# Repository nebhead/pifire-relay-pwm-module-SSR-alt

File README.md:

# PiFire Solid State Relay (SSR) Module PCB ALT (v1.0.0-alt) KiCad Files

## What is this? 

This PCB is designed to support SSR relays for controlling incoming Power(L) to the Igniter and Auger.  This board also has circuitry to support a 12V PWM fan.  This board uses compact solid state relays that are able to handle high power. This is an alternative to using an off the shelf relay module which simplifies the wiring and even allows you to use the OEM harness.

This version of the board was designed with help from user @labmonkeyrat on Discord. PCB mounted fuses have been removed, preferring inline fuses external to the board. The fan power is controlled from the high side (12V) instead of ground (original design).  

The design intent for this board was to make a DIY accessible PCB that can be more easily put together by the maker/enthusiast of almost any skill level.  Full size components are used in most cases and most (if not all) parts should be readily available to order online.  See the [Interactive BOM](#interactive-bom) for more details about the parts used and links to order.

### Important Notes

This PCB is intended to be used with the 4.0.x PCB design ([linked below](#links-to-the-pcbs-in-this-family-of-pifire-boards)) in conjunction with v1.8.x or later of the PiFire software.

The G3MB Relay footprints have been left out of this release because they were sourced from SnapMagic (for free), but are not licensed for re-distribution.  If you plan to edit this board, you may need to source those files from SnapMagic directly and add them to this project in the G3MB folder.

### What is PiFire? 

PiFire is a SBC based Pellet Smoker Controller.  More details can be found [here](https://nebhead.github.io/PiFire) or [at the GitHub repo](https://github.com/nebhead/pifire). 

## What's in this Repository?

### KiCad Project Files 
In this repository you will find the latest KiCad design files for the  PCB.  Simply load the project file (.kicad_pro) into the KiCad software and you should be able to edit as needed.  Or if you just want to get this board made, jump to the production section below.

### Interactive BOM

There is an interactive BOM located in the [/bom](bom/) folder which details the parts and provides some pin information as well.  Use this to gather the components you may need to build this board out and refer back to it for placement help.    

[BOM + Pin Info](https://nebhead.github.io/pifire-relay-pwm-module-SSR-alt)

_This is a standalone HTML file that was autogenerated by the excellent plugin for KiCad. See the plugin here: [https://github.com/openscopeproject/InteractiveHtmlBom](https://github.com/openscopeproject/InteractiveHtmlBom)_

### PDF of the Schematic

Preview the schematic in PDF format here: [Schematic](schematic.pdf)

### PWM Fan Pinout

The PWM fan pinout is using a standard 4-pin fan connector.  It's recommended to source the headers with retaining clip to ensure that the fan doesn't easily come unplugged.  JST headers can be used as well. 

### JLCPCB Production Files

If you wish to get these PCBs made by JLCPCB, the production files are provided in the `/production` folder.  For convenience, the file `production.zip` can simply be uploaded to JLCPCB to make it super easy to order boards.

Drop the zip file onto the order page, wait for it to upload then simply continue to order the board.  Optionally, select different board color, PCB quantity, surface finish, etc.  Most of the default settings should be sufficient. 

### Links to the PCBs in this family of PiFire Boards

This PCB is part of a family of PCBs that can be used together to create  a full PiFire system.  Generally speaking you need the Main Module/Board, a Relay Control Board and a Probe Device board to have a basic PiFire system.  

**Main Module/Board** (required)
* [Main Board v4.0.x](https://github.com/nebhead/pifire-main-module-nopwr)

**Relay/Fan Control Boards** (choose one)
* [Mechanical Relay Module](https://github.com/nebhead/pifire-relay-module)
* [Solid State Relay Module](https://github.com/nebhead/pifire-relay-module-ssr)
* [Solid State Relay + PWM Fan Module](https://github.com/nebhead/pifire-relay-pwm-module-ssr) - Original Design
* [Solid State Relay + PWM Fan Module Alternate](https://github.com/nebhead/pifire-relay-pwm-module-ssr-alt) - Updated Design (Designed with help from @labmonkeyrat on Discord)

**Probe Device Board** (optional)
* [ADS Board](https://github.com/nebhead/pifire-ads-board) 

### 3D Printable Enclosures/Boxes 

With all of the 3D Prints for PiFire, a higher temperature filament such as PETG should be used.  PLA generally won't stand up to the temperatures that the components may be exposed to outdoors and near a hot smoker.  

#### Enclosure

Included here is an initial revision of the enclosure for this PCB.  The current models should be considered still in development and may have alignment challenges, etc. 

Except for the mounting wings, the majority of bolts to be used with this enclosure are M3. 

* STL: [Base](/printables/PiFire-v4-Relay-Base.stl)
* STL: [Lid](/printables/PiFire-v4-Relay-Lid.stl)
* OnShape: [Enclosure Original Models](https://cad.onshape.com/documents/03559f76f7adf190bf6f1259/w/7529cb0e4cd69db1a6a15202/e/07d5f9d46dc8f2b9e7dd655f?renderMode=0&uiState=66e11de950d7684b88999a0f)

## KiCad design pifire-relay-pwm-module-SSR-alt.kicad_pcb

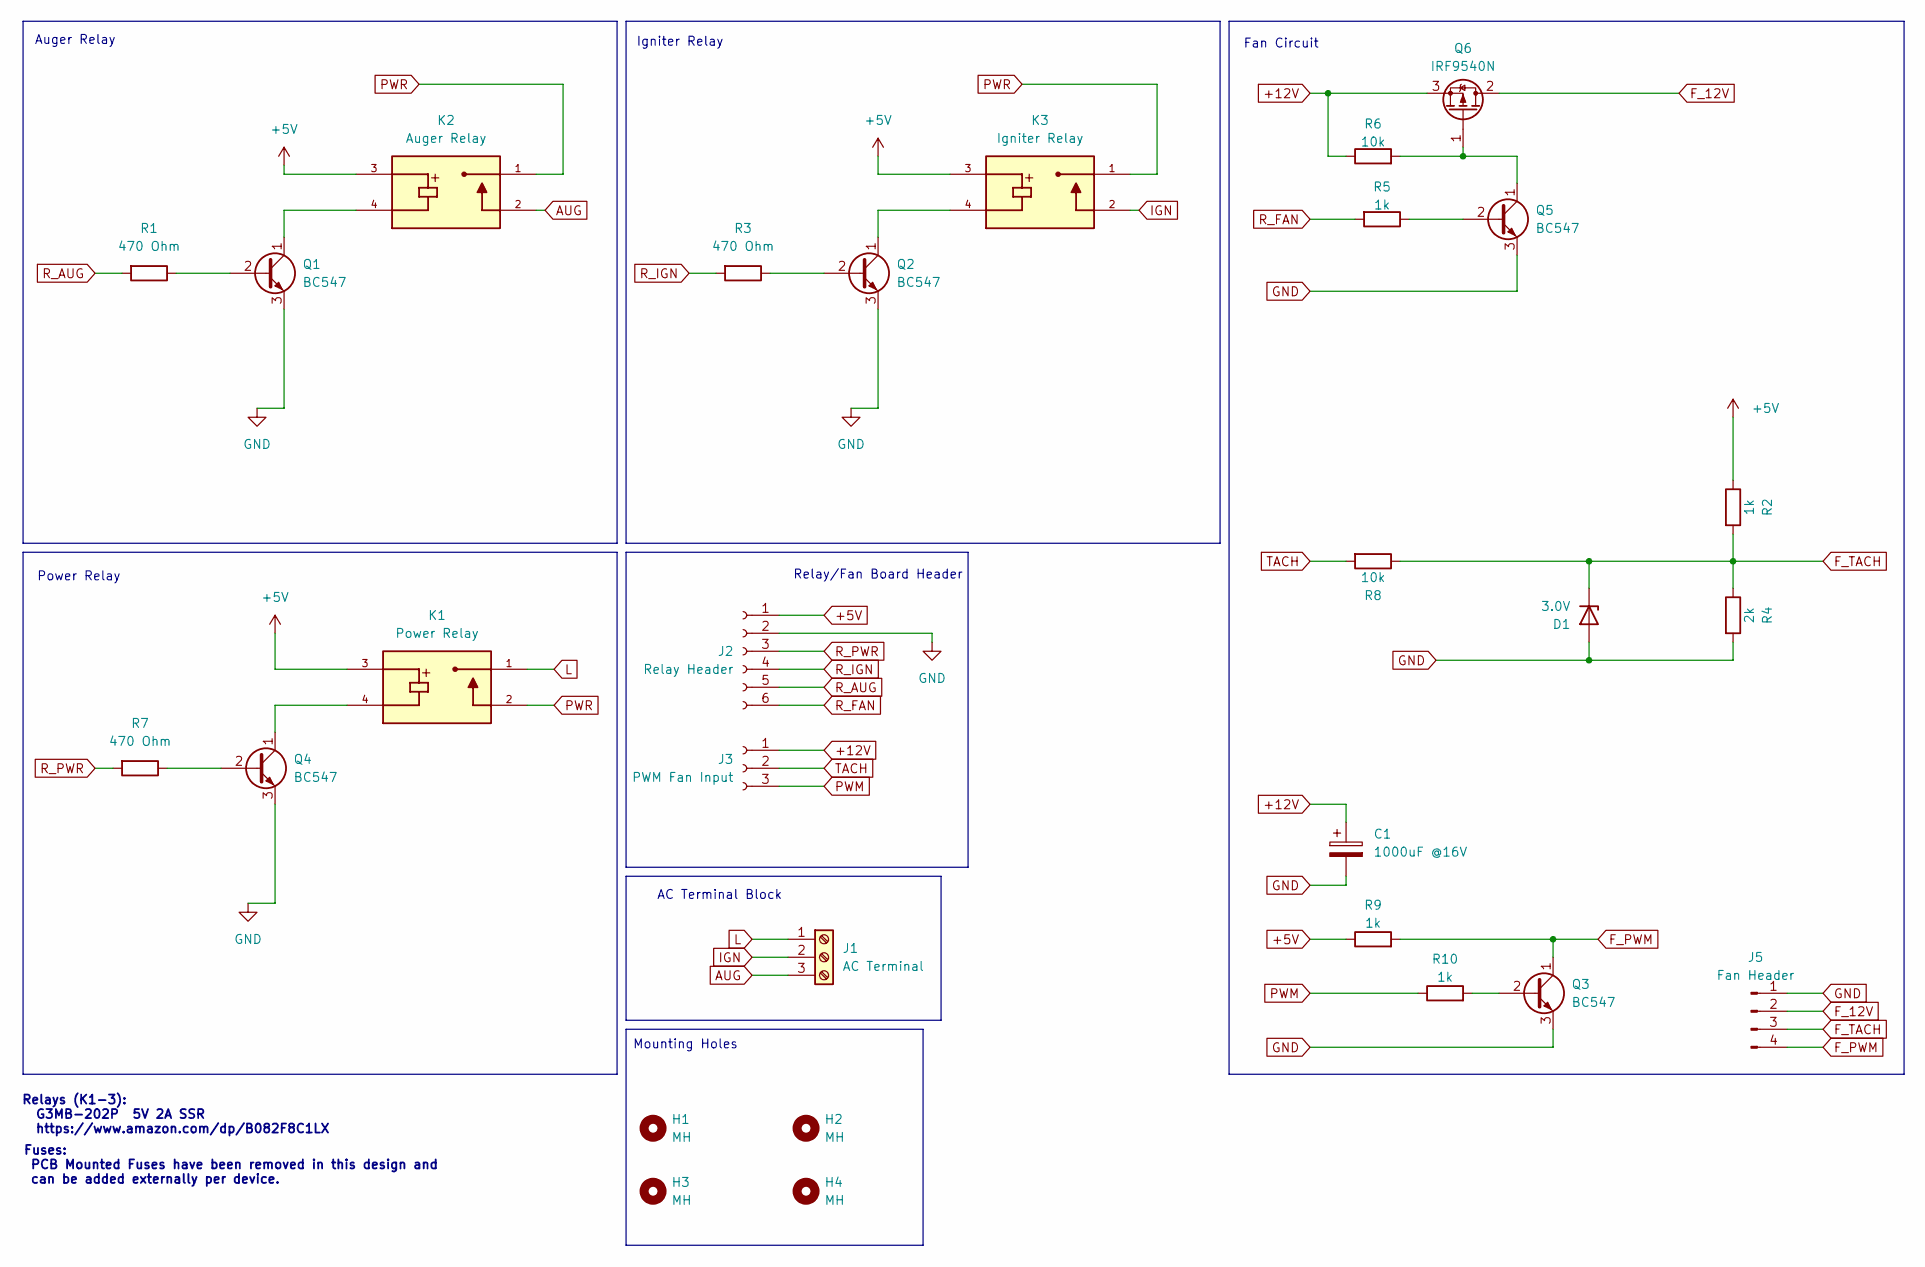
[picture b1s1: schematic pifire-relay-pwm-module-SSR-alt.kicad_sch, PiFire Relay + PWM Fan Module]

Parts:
C1: 1000uF @16V; CP_Radial_D6.3mm_P2.50mm
D1: 3.0V; D_DO-41_SOD81_P7.62mm_Horizontal
H1, H2, H3, H4: MH; MountingHole_3.2mm_M3
J1: AC Terminal; TerminalBlock_bornier-3_P5.08mm
J2: Relay Header; JST_XH_B6B-XH-A_1x06_P2.50mm_Vertical
J3: PWM Fan Input; JST_XH_B3B-XH-A_1x03_P2.50mm_Vertical
J5: Fan Header; FanPinHeader_1x04_P2.54mm_Vertical
K1: Power Relay; RELAY_G3MB-202PDC5; PARTREV J091-E1-1A
K2: Auger Relay; RELAY_G3MB-202PDC5; PARTREV J091-E1-1A
K3: Igniter Relay; RELAY_G3MB-202PDC5; PARTREV J091-E1-1A
Q1, Q2, Q3, Q4, Q5: BC547; TO-92L_Inline
Q6: IRF9540N; TO-220-3_Vertical
R1, R3, R7: 470 Ohm; R_Axial_DIN0207_L6.3mm_D2.5mm_P7.62mm_Horizontal
R2, R5, R9, R10: 1k; R_Axial_DIN0207_L6.3mm_D2.5mm_P7.62mm_Horizontal
R4: 2k; R_Axial_DIN0207_L6.3mm_D2.5mm_P7.62mm_Horizontal
R6, R8: 10k; R_Axial_DIN0207_L6.3mm_D2.5mm_P7.62mm_Horizontal

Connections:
+5V: J2.1, K1.3, K2.3, K3.3, R2.1, R9.1
+12V: C1.1, J3.1, Q6.3 (S), R6.1
AUG: J1.3, K2.2
F_12V: J5.2, Q6.2 (D)
F_PWM: J5.4, Q3.1 (C), R9.2
F_TACH: D1.1 (K), J5.3, R2.2, R4.1, R8.1
GND: C1.2, D1.2 (A), J2.2, J5.1, Q1.3 (E), Q2.3 (E), Q3.3 (E), Q4.3 (E), Q5.3 (E), R4.2
IGN: J1.2, K3.2
L: J1.1, K1.1
unnamed: Q1.2 (B), R1.1
unnamed: K2.4, Q1.1 (C)
unnamed: Q2.2 (B), R3.1
unnamed: K3.4, Q2.1 (C)
unnamed: Q3.2 (B), R10.2
unnamed: Q4.2 (B), R7.1
unnamed: K1.4, Q4.1 (C)
unnamed: Q5.2 (B), R5.1
unnamed: Q5.1 (C), Q6.1 (G), R6.2
PWM: J3.3, R10.1
PWR: K1.2, K2.1, K3.1
R_AUG: J2.5, R1.2
R_FAN: J2.6, R5.2
R_IGN: J2.4, R3.2
R_PWR: J2.3, R7.2
TACH: J3.2, R8.2

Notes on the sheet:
Fan Circuit
Power Relay
Fuses: PCB Mounted Fuses have been removed in this design and can be added externally per device.
AC Terminal Block
Auger Relay
Relay/Fan Board Header
Relays (K1-3): G3MB-202P 5V 2A SSR https://www.amazon.com/dp/B082F8C1LX
Mounting Holes
Igniter Relay

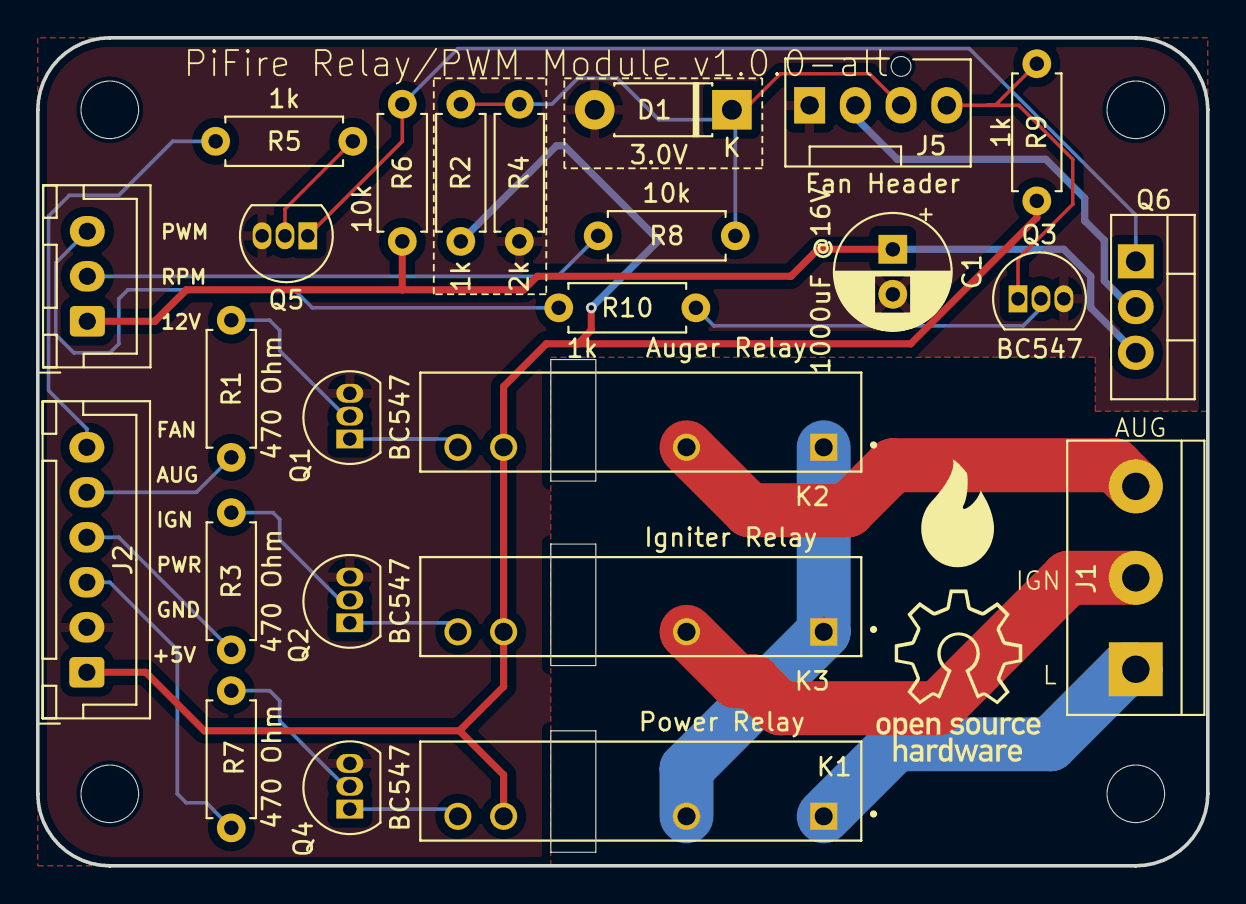
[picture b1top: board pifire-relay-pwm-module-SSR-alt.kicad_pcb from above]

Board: 2 copper layers, 65.0 x 46.0 mm, 29 parts (0 on the bottom side), 25 nets.

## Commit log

2024-09-07 Adding Project Files
2024-09-07 Updated Production Files with Latest
2024-09-07 Add board image
2024-09-11 Added 3D Printables
2025-04-16 Updated with PWM Fan Pinout
